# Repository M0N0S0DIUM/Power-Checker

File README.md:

# [DevGuard 24](https://www.tindie.com/products/41136/)  
### Inline 3–24V Protection Module

<p align="center">
  <!-- Replace with actual image -->
  
</p>

--- 

DevGuard 24 is a compact inline protection module designed to protect low-voltage electronics from reverse polarity, overload, and voltage transients.

Plug it between your power source and your project.

No configuration. No setup. Just protection.

---

## Overview

Ever fried a dev board from a reversed power connection?

DevGuard 24 is designed to prevent exactly that. It sits inline between your power source and your circuit, blocking reverse polarity and clamping voltage spikes before they reach your hardware.

The protection topology combines:

- P-channel MOSFET reverse polarity protection  
- Resettable polyfuse for overcurrent protection  
- TVS diode for transient voltage suppression  

Together, these provide robust protection against common wiring mistakes and unexpected electrical events.

---

## Technical Specifications

**Input Voltage Range:**  
3 V – 24 V DC

**Protection Features:**  
- Reverse polarity blocking  
- Transient voltage suppression (TVS clamp)  
- Resettable polyfuse overcurrent protection  

**Fuse Options:**

- 500 mA version — for small loads and dev boards  
- 1100 mA version — for heavier circuits  

**Connections:**  
Inline screw terminal input and output

---

## How It Works

Under normal operation, the P-MOSFET allows current to flow with minimal voltage drop.

If power is connected backwards, the MOSFET blocks reverse current, preventing damage to downstream electronics.

If a surge or transient spike occurs, the TVS diode clamps excessive voltage.

If sustained overcurrent occurs, the polyfuse trips and limits current. Once the fault is removed, it automatically resets.

---

## Intended Use

DevGuard 24 is intended for:

- Prototyping and development work
- Bench testing embedded systems
- Protecting dev boards and small circuits
- Inline protection for experimental builds
- Field testing unknown power sources

---

## Limitations

- Not a regulated power supply
- Not designed for high-current motor loads
- Not a replacement for proper system-level protection design
- Not intended for extreme industrial or high-energy environments

Always verify suitability for your specific application.

---

## Why It Exists

We’ve all done it.

It’s late. You’re deep into a build. You swap leads. Power on.

Smoke.

DevGuard 24 is inexpensive insurance for those moments when your brain is already three problems ahead of your hands.

Small enough to tuck into almost any setup. Simple enough to use without thinking about it.

---

## What’s Included

- 1× DevGuard 24 module (500 mA or 1100 mA version)

No cables or enclosure included.

[Buy here](https://www.tindie.com/products/41136/)

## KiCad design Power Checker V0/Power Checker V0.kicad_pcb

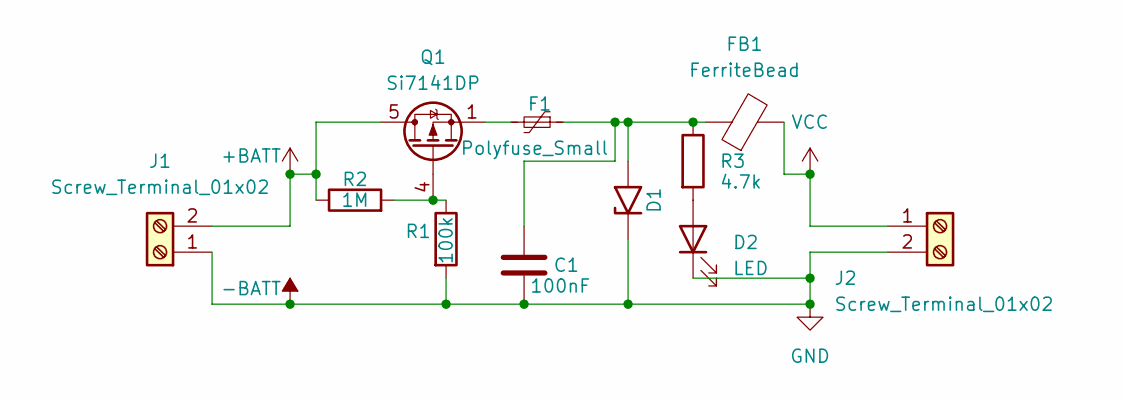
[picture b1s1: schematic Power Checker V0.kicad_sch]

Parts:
C1: 100nF; C_0201_0603Metric_Pad0.64x0.40mm_HandSolder
D1: SMAJ24A; D_SMA
D2: LED; LED_0603_1608Metric_Pad1.05x0.95mm_HandSolder
F1: Polyfuse_Small; C_1812_4532Metric_Pad1.57x3.40mm_HandSolder
FB1: FerriteBead; L_0603_1608Metric_Pad1.05x0.95mm_HandSolder
J1, J2: Screw_Terminal_01x02; Altech_AK100_1x02_P5.00mm
Q1: Si7141DP; PowerPAK_SO-8_Single
R1: 100k; R_0402_1005Metric_Pad0.72x0.64mm_HandSolder
R2: 1M; R_0402_1005Metric_Pad0.72x0.64mm_HandSolder
R3: 4.7k; C_0201_0603Metric_Pad0.64x0.40mm_HandSolder

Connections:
+BATT: J1.2, Q1.5 (D), R2.1
-BATT: C1.2, D1.1 (A1), D2.1 (K), J1.1, J2.2, R1.2
unnamed: C1.1, D1.2 (A2), F1.1, FB1.1, R3.1
unnamed: D2.2 (A), R3.2
unnamed: F1.2, Q1.1 (S), Q1.2 (S), Q1.3 (S)
unnamed: Q1.4 (G), R1.1, R2.2
VCC: FB1.2, J2.1

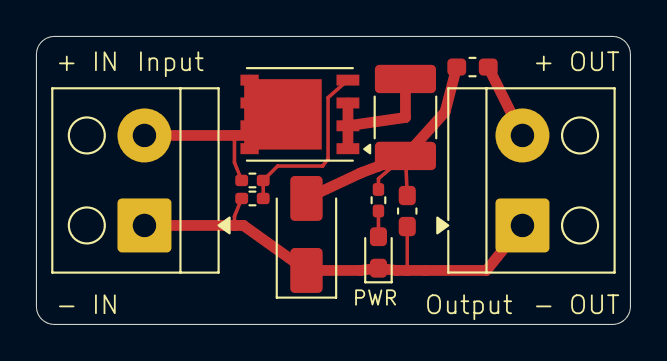
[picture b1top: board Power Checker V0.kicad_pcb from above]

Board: 2 copper layers, 33.0 x 16.0 mm, 11 parts (0 on the bottom side), 7 nets.
